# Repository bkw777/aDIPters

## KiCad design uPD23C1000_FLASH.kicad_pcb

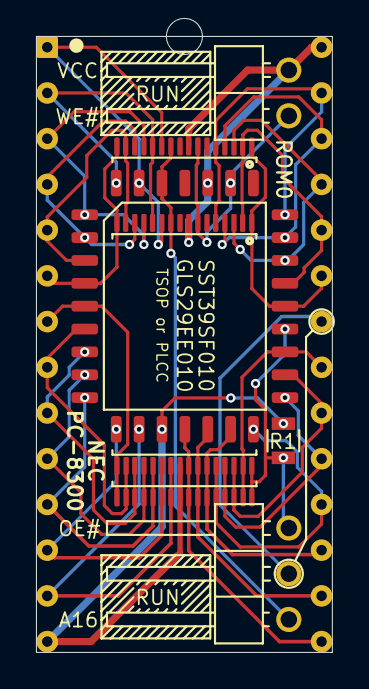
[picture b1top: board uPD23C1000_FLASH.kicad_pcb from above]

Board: 2 copper layers, 16.4 x 34.2 mm, 7 parts (0 on the bottom side), 31 nets.

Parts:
J1: uPD23C1000; DIP-28_W15.24mm_pcb_sil_pins
J2: Conn_1x2; Pin_Header_Angled_1x02_Pitch2.54mm
J3: Conn_1x3; Pin_Header_Angled_1x03_Pitch2.54mm
R1: 47k; R_0805
U1: GLS29EE010 (TSOP); TSOP32-20mm
U2: SST39SF010 (TSOP); TSOP32-14mm
U3: SST39SF010 / GLS29EE010 (PLCC); PLCC32_7x9

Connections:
/A0: J1.10, U1.20, U2.20, U3.12
/A1: J1.9, U1.19, U2.19, U3.11
/A2: J1.8, U1.18, U2.18, U3.10
/A3: J1.7, U1.17, U2.17, U3.9
/A4: J1.6, U1.16, U2.16, U3.8
/A5: J1.5, U1.15, U2.15, U3.7
/A6: J1.4, U1.14, U2.14, U3.6
/A7: J1.3, U1.13, U2.13, U3.5
/A8: J1.25, U1.3, U2.3, U3.27
/A9: J1.24, U1.2, U2.2, U3.26
/A10: J1.21, U1.31, U2.31, U3.23
/A11: J1.23, U1.1, U2.1, U3.25
/A12: J1.2, U1.12, U2.12, U3.4
/A13: J1.26, U1.4, U2.4, U3.28
/A14: J1.27, U1.5, U2.5, U3.29
/A15: J1.1, U1.11, U2.11, U3.3
/A16: J3.1, U1.10, U2.10, U3.2
/A16_OE: J1.22, J3.2
/D0: J1.11, U1.21, U2.21, U3.13
/D1: J1.12, U1.22, U2.22, U3.14
/D2: J1.13, U1.23, U2.23, U3.15
/D3: J1.15, U1.25, U2.25, U3.17
/D4: J1.16, U1.26, U2.26, U3.18
/D5: J1.17, U1.27, U2.27, U3.19
/D6: J1.18, U1.28, U2.28, U3.20
/D7: J1.19, U1.29, U2.29, U3.21
/GND: J1.14, R1.2, U1.24, U2.24, U3.16
/VCC: J1.28, J2.2, U1.8, U2.8, U3.32
/~CE: J1.20, U1.30, U2.30, U3.22
/~OE: J3.3, R1.1, U1.32, U2.32, U3.24
/~WE: J2.1, U1.7, U2.7, U3.31

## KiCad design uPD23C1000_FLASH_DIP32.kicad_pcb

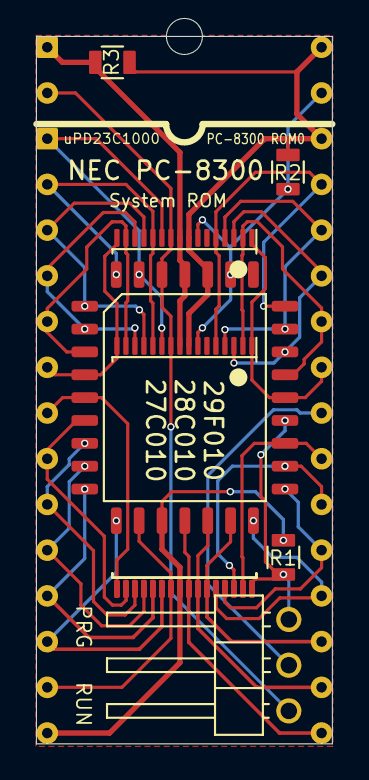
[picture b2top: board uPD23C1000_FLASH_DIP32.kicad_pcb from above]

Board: 2 copper layers, 16.4 x 39.3 mm, 8 parts (0 on the bottom side), 32 nets.

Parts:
J1: uPD23C1000 / FLASH; DIP32_0.6_pcb_sil_pins
JP1: RUN/PROGRAM; Pin_Header_Angled_1x03_Pitch2.54mm_12shorted
R1: 47k; R_0805
R2, R3: 47K; R_0805
U1: GLS29EE010 (TSOP); TSOP32-20mm
U2: SST39SF010 (TSOP); TSOP32-14mm
U3: SST39SF010 / GLS29EE010 (PLCC); PLCC32_7x9

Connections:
/A0: J1.12, U1.20, U2.20, U3.12
/A1: J1.11, U1.19, U2.19, U3.11
/A2: J1.10, U1.18, U2.18, U3.10
/A3: J1.9, U1.17, U2.17, U3.9
/A4: J1.8, U1.16, U2.16, U3.8
/A5: J1.7, U1.15, U2.15, U3.7
/A6: J1.6, U1.14, U2.14, U3.6
/A7: J1.5, U1.13, U2.13, U3.5
/A8: J1.27, U1.3, U2.3, U3.27
/A9: J1.26, U1.2, U2.2, U3.26
/A10: J1.23, U1.31, U2.31, U3.23
/A11: J1.25, U1.1, U2.1, U3.25
/A12: J1.4, U1.12, U2.12, U3.4
/A13: J1.28, U1.4, U2.4, U3.28
/A14: J1.29, U1.5, U2.5, U3.29
/A15: J1.3, U1.11, U2.11, U3.3
/A16: J1.2, JP1.1, U1.10, U2.10, U3.2
/A16_~OE: J1.24, JP1.2
/D0: J1.13, U1.21, U2.21, U3.13
/D1: J1.14, U1.22, U2.22, U3.14
/D2: J1.15, U1.23, U2.23, U3.15
/D3: J1.17, U1.25, U2.25, U3.17
/D4: J1.18, U1.26, U2.26, U3.18
/D5: J1.19, U1.27, U2.27, U3.19
/D6: J1.20, U1.28, U2.28, U3.20
/D7: J1.21, U1.29, U2.29, U3.21
/GND: J1.16, R1.2, U1.24, U2.24, U3.16
/VCC: J1.30, J1.32, R2.2, R3.2, U1.8, U2.8, U3.32
/VPP: J1.1, R3.1, U1.9, U2.9, U3.1
/~CE: J1.22, U1.30, U2.30, U3.22
/~OE: JP1.3, R1.1, U1.32, U2.32, U3.24
/~WE: J1.31, R2.1, U1.7, U2.7, U3.31

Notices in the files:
parts and their libraries:
Copyright 2016 Accelerated Designs. All rights reserved.
